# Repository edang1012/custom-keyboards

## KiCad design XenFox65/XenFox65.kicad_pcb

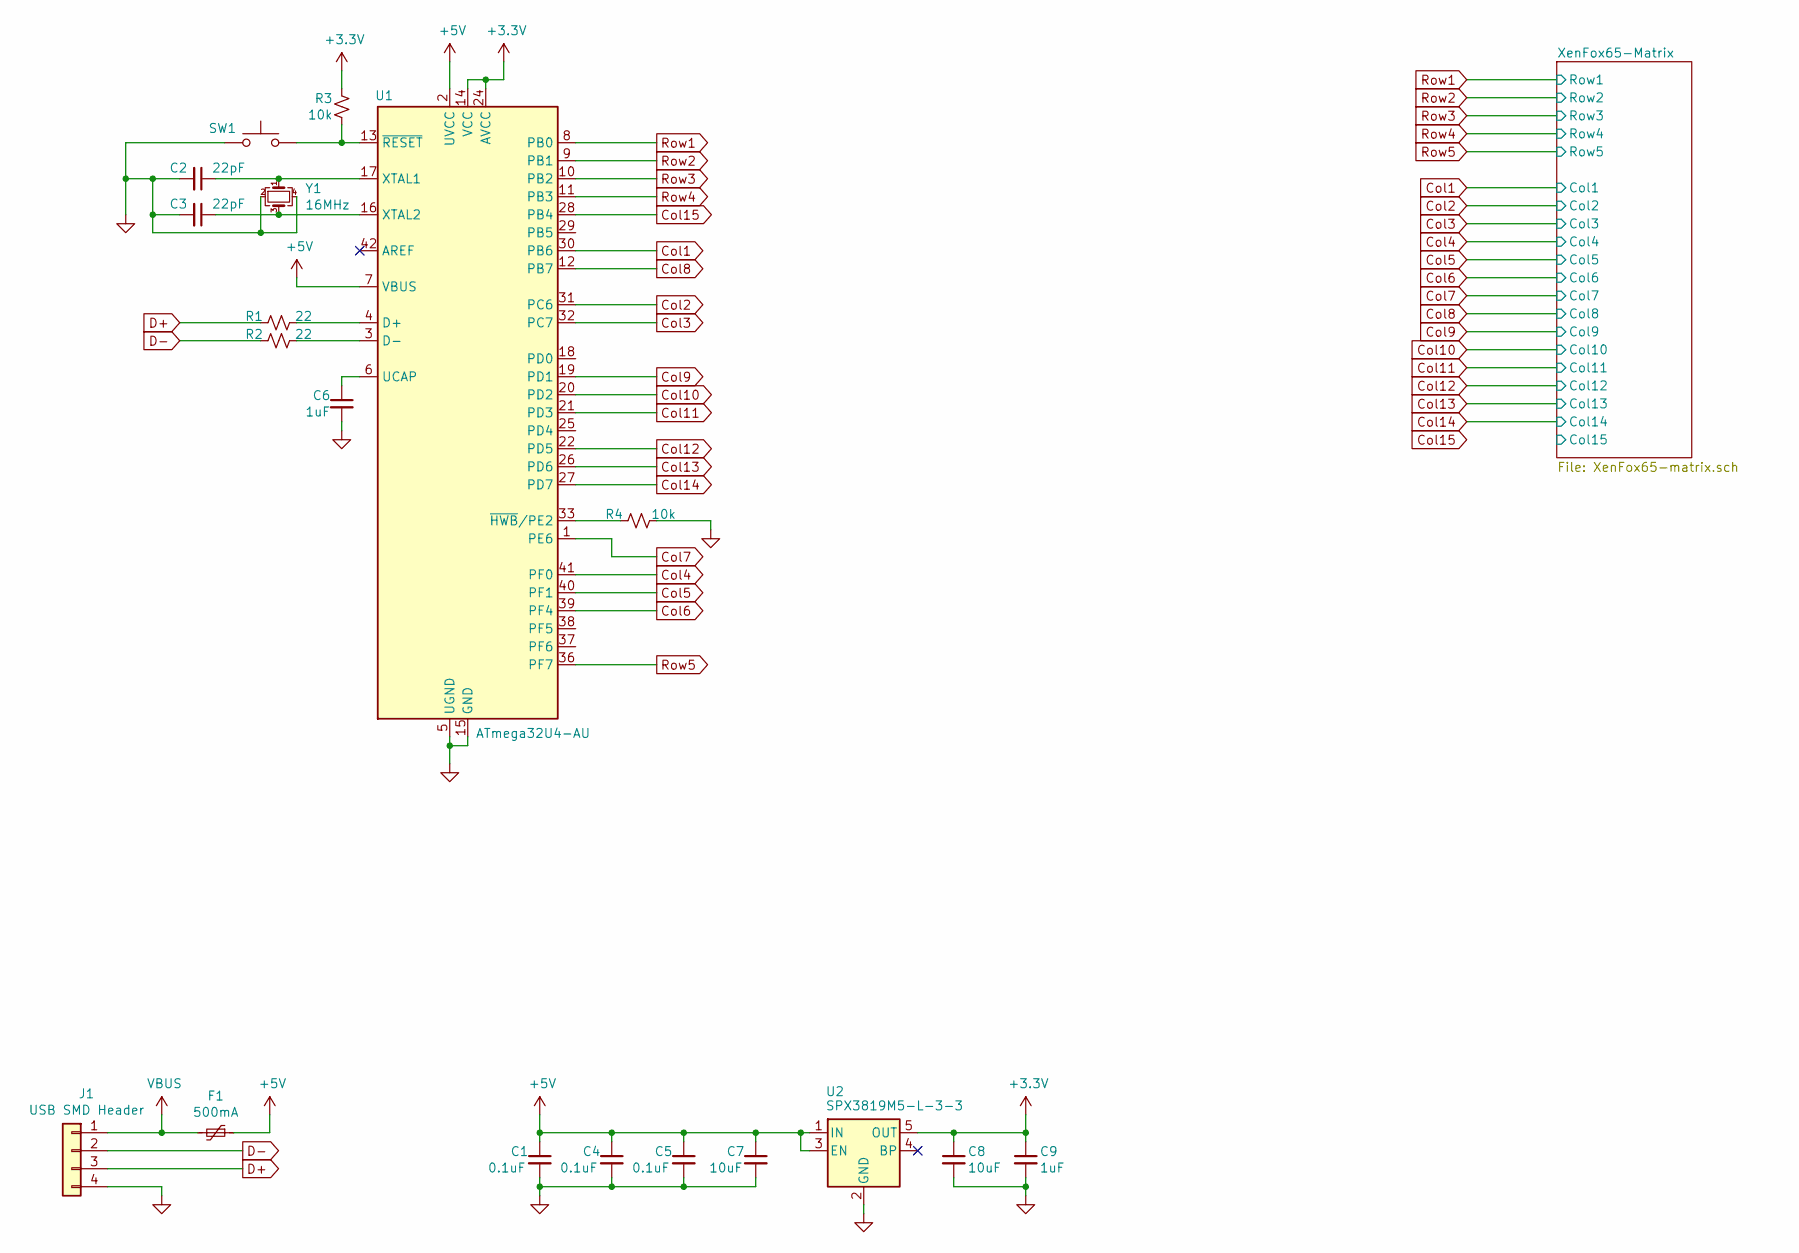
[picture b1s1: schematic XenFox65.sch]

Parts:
C1, C4, C5: 0.1uF; C_0805_2012Metric
C2, C3: 22pF; C_0805_2012Metric
C6, C9: 1uF; C_0805_2012Metric
C7, C8: 10uF; C_0805_2012Metric
F1: 500mA; Fuse_1206_3216Metric_Pad1.42x1.75mm_HandSolder
J1: USB SMD Header; S4B-ZR
R1, R2: 22; R_0805_2012Metric_Pad1.15x1.40mm_HandSolder
R3, R4: 10k; R_0805_2012Metric_Pad1.15x1.40mm_HandSolder
SW1: SW_Push; SKQG-1155865
U1: ATmega32U4-AU; TQFP-44_10x10mm_P0.8mm
U2: SPX3819M5-L-3-3; SOT-23-5
Y1: 16MHz; Crystal_SMD_3225-4Pin_3.2x2.5mm_HandSoldering

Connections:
+3V3: C8.1, C9.1, R3.1, U1.14 (VCC), U1.24 (AVCC), U1.34 (VCC), U1.44 (AVCC), U2.5 (OUT)
+5V: C1.1, C4.1, C5.1, C7.1, F1.1, U1.2 (UVCC), U1.7 (VBUS), U2.1 (IN), U2.3 (EN)
Col1: U1.30 (PB6); also elsewhere on the board
Col2: U1.31 (PC6); also elsewhere on the board
Col3: U1.32 (PC7); also elsewhere on the board
Col4: U1.41 (PF0); also elsewhere on the board
Col5: U1.40 (PF1); also elsewhere on the board
Col6: U1.39 (PF4); also elsewhere on the board
Col7: U1.1 (PE6); also elsewhere on the board
Col8: U1.12 (PB7); also elsewhere on the board
Col9: U1.19 (PD1); also elsewhere on the board
Col10: U1.20 (PD2); also elsewhere on the board
Col11: U1.21 (PD3); also elsewhere on the board
Col12: U1.22 (PD5); also elsewhere on the board
Col13: U1.26 (PD6); also elsewhere on the board
Col14: U1.27 (PD7); also elsewhere on the board
Col15: U1.28 (PB4); also elsewhere on the board
D+: J1.3, R1.2
D-: J1.2, R2.2
GND: C1.2, C2.2, C3.2, C4.2, C5.2, C6.2, C7.2, C8.2, C9.2, J1.4, R4.1, SW1.1, U1.5 (UGND), U1.15 (GND), U1.23 (GND), U1.35 (GND), U1.43 (GND), U2.2 (GND), Y1.2, Y1.4
unnamed: C2.1, U1.17 (XTAL1), Y1.1
unnamed: C3.1, U1.16 (XTAL2), Y1.3
unnamed: C6.1, U1.6 (UCAP)
unnamed: R1.1, U1.4 (D+)
unnamed: R2.1, U1.3 (D-)
unnamed: R3.2, SW1.2, U1.13 (~RESET)
unnamed: R4.2, U1.33 (~HWB~/PE2)
Row1: U1.8 (PB0); also elsewhere on the board
Row2: U1.9 (PB1); also elsewhere on the board
Row3: U1.10 (PB2); also elsewhere on the board
Row4: U1.11 (PB3); also elsewhere on the board
Row5: U1.36 (PF7); also elsewhere on the board
VBUS: F1.2, J1.1

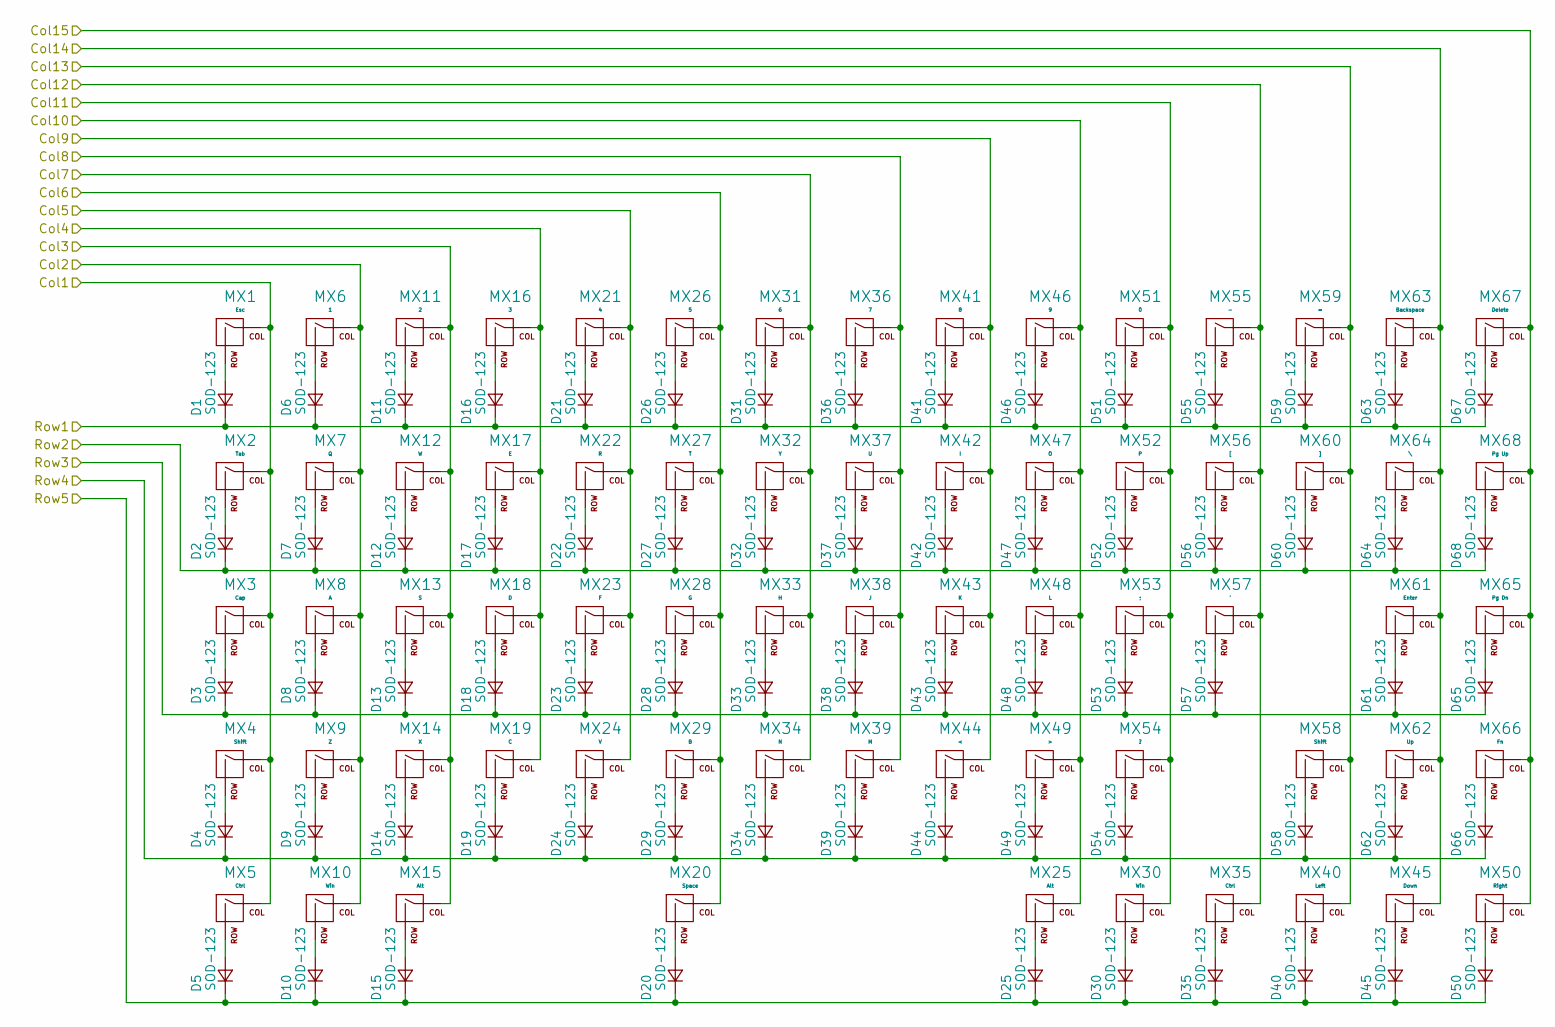
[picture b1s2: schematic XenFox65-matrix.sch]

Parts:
D1, D2, D3, D4, D5, D6, D7, D8, D9, D10, D11, D12, D13, D14, D15, D16, D17, D18, D19, D20, D21, D22, D23, D24, D25, D26, D27, D28, D29, D30, D31, D32, D33, D34, D35, D36, D37, D38, D39, D40, D41, D42, D43, D44, D45, D46, D47, D48, D49, D50, D51, D52, D53, D54, D55, D56, D57, D58, D59, D60, D61, D62, D63, D64, D65, D66, D67, D68: SOD-123; D_SOD-123
MX1: Esc; MXOnly-1U-NoLED
MX2: Tab; MXOnly-1.5U-NoLED
MX3: Cap; MXOnly-1.75U-NoLED
MX4: Shift; MXOnly-2.25U-NoLED
MX5: Ctrl; MXOnly-1.25U-NoLED
MX6: 1; MXOnly-1U-NoLED
MX7: Q; MXOnly-1U-NoLED
MX8: A; MXOnly-1U-NoLED
MX9: Z; MXOnly-1U-NoLED
MX10: Win; MXOnly-1.25U-NoLED
MX11: 2; MXOnly-1U-NoLED
MX12: W; MXOnly-1U-NoLED
MX13: S; MXOnly-1U-NoLED
MX14: X; MXOnly-1U-NoLED
MX15: Alt; MXOnly-1.25U-NoLED
MX16: 3; MXOnly-1U-NoLED
MX17: E; MXOnly-1U-NoLED
MX18: D; MXOnly-1U-NoLED
MX19: C; MXOnly-1U-NoLED
MX20: Space; MXOnly-6.25U-ReversedStabilizers-NoLED
MX21: 4; MXOnly-1U-NoLED
MX22: R; MXOnly-1U-NoLED
MX23: F; MXOnly-1U-NoLED
MX24: V; MXOnly-1U-NoLED
MX25: Alt; MXOnly-1U-NoLED
MX26: 5; MXOnly-1U-NoLED
MX27: T; MXOnly-1U-NoLED
MX28: G; MXOnly-1U-NoLED
MX29: B; MXOnly-1U-NoLED
MX30: Win; MXOnly-1U-NoLED
MX31: 6; MXOnly-1U-NoLED
MX32: Y; MXOnly-1U-NoLED
MX33: H; MXOnly-1U-NoLED
MX34: N; MXOnly-1U-NoLED
MX35: Ctrl; MXOnly-1U-NoLED
MX36: 7; MXOnly-1U-NoLED
MX37: U; MXOnly-1U-NoLED
MX38: J; MXOnly-1U-NoLED
MX39: M; MXOnly-1U-NoLED
MX40: Left; MXOnly-1U-NoLED
MX41: 8; MXOnly-1U-NoLED
MX42: I; MXOnly-1U-NoLED
MX43: K; MXOnly-1U-NoLED
MX44: <; MXOnly-1U-NoLED
MX45: Down; MXOnly-1U-NoLED
MX46: 9; MXOnly-1U-NoLED
MX47: O; MXOnly-1U-NoLED
MX48: L; MXOnly-1U-NoLED
MX49: >; MXOnly-1U-NoLED
MX50: Right; MXOnly-1U-NoLED
MX51: 0; MXOnly-1U-NoLED
MX52: P; MXOnly-1U-NoLED
MX53: ;; MXOnly-1U-NoLED
MX54: ?; MXOnly-1U-NoLED
MX55: -; MXOnly-1U-NoLED
MX56: [; MXOnly-1U-NoLED
MX57: '; MXOnly-1U-NoLED
MX58: Shift; MXOnly-1.75U-NoLED
MX59: =; MXOnly-1U-NoLED
MX60: ]; MXOnly-1U-NoLED
MX61: Enter; MXOnly-2.25U-NoLED
MX62: Up; MXOnly-1U-NoLED
MX63: Backspace; MXOnly-2U-NoLED
MX64: \\; MXOnly-1.5U-NoLED
MX65: Pg Dn; MXOnly-1U-NoLED
MX66: Fn; MXOnly-1U-NoLED
MX67: Delete; MXOnly-1U-NoLED
MX68: Pg Up; MXOnly-1U-NoLED

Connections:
Col1: MX1.1 (COL), MX2.1 (COL), MX3.1 (COL), MX4.1 (COL), MX5.1 (COL); also elsewhere on the board
Col2: MX6.1 (COL), MX7.1 (COL), MX8.1 (COL), MX9.1 (COL), MX10.1 (COL); also elsewhere on the board
Col3: MX11.1 (COL), MX12.1 (COL), MX13.1 (COL), MX14.1 (COL), MX15.1 (COL); also elsewhere on the board
Col4: MX16.1 (COL), MX17.1 (COL), MX18.1 (COL), MX19.1 (COL); also elsewhere on the board
Col5: MX21.1 (COL), MX22.1 (COL), MX23.1 (COL), MX24.1 (COL); also elsewhere on the board
Col6: MX20.1 (COL), MX26.1 (COL), MX27.1 (COL), MX28.1 (COL), MX29.1 (COL); also elsewhere on the board
Col7: MX31.1 (COL), MX32.1 (COL), MX33.1 (COL), MX34.1 (COL); also elsewhere on the board
Col8: MX36.1 (COL), MX37.1 (COL), MX38.1 (COL), MX39.1 (COL); also elsewhere on the board
Col9: MX41.1 (COL), MX42.1 (COL), MX43.1 (COL), MX44.1 (COL); also elsewhere on the board
Col10: MX25.1 (COL), MX46.1 (COL), MX47.1 (COL), MX48.1 (COL), MX49.1 (COL); also elsewhere on the board
Col11: MX30.1 (COL), MX51.1 (COL), MX52.1 (COL), MX53.1 (COL), MX54.1 (COL); also elsewhere on the board
Col12: MX35.1 (COL), MX55.1 (COL), MX56.1 (COL), MX57.1 (COL); also elsewhere on the board
Col13: MX40.1 (COL), MX58.1 (COL), MX59.1 (COL), MX60.1 (COL); also elsewhere on the board
Col14: MX45.1 (COL), MX61.1 (COL), MX62.1 (COL), MX63.1 (COL), MX64.1 (COL); also elsewhere on the board
Col15: MX50.1 (COL), MX65.1 (COL), MX66.1 (COL), MX67.1 (COL), MX68.1 (COL); also elsewhere on the board
unnamed: D1.2 (A), MX1.2 (ROW)
unnamed: D2.2 (A), MX2.2 (ROW)
unnamed: D3.2 (A), MX3.2 (ROW)
unnamed: D4.2 (A), MX4.2 (ROW)
unnamed: D5.2 (A), MX5.2 (ROW)
unnamed: D6.2 (A), MX6.2 (ROW)
unnamed: D7.2 (A), MX7.2 (ROW)
unnamed: D8.2 (A), MX8.2 (ROW)
unnamed: D9.2 (A), MX9.2 (ROW)
unnamed: D10.2 (A), MX10.2 (ROW)
unnamed: D11.2 (A), MX11.2 (ROW)
unnamed: D12.2 (A), MX12.2 (ROW)
unnamed: D13.2 (A), MX13.2 (ROW)
unnamed: D14.2 (A), MX14.2 (ROW)
unnamed: D15.2 (A), MX15.2 (ROW)
unnamed: D16.2 (A), MX16.2 (ROW)
unnamed: D17.2 (A), MX17.2 (ROW)
unnamed: D18.2 (A), MX18.2 (ROW)
unnamed: D19.2 (A), MX19.2 (ROW)
unnamed: D20.2 (A), MX20.2 (ROW)
unnamed: D21.2 (A), MX21.2 (ROW)
unnamed: D22.2 (A), MX22.2 (ROW)
unnamed: D23.2 (A), MX23.2 (ROW)
unnamed: D24.2 (A), MX24.2 (ROW)
unnamed: D25.2 (A), MX25.2 (ROW)
unnamed: D26.2 (A), MX26.2 (ROW)
unnamed: D27.2 (A), MX27.2 (ROW)
unnamed: D28.2 (A), MX28.2 (ROW)
unnamed: D29.2 (A), MX29.2 (ROW)
unnamed: D30.2 (A), MX30.2 (ROW)
unnamed: D31.2 (A), MX31.2 (ROW)
unnamed: D32.2 (A), MX32.2 (ROW)
unnamed: D33.2 (A), MX33.2 (ROW)
unnamed: D34.2 (A), MX34.2 (ROW)
unnamed: D35.2 (A), MX35.2 (ROW)
unnamed: D36.2 (A), MX36.2 (ROW)
unnamed: D37.2 (A), MX37.2 (ROW)
unnamed: D38.2 (A), MX38.2 (ROW)
unnamed: D39.2 (A), MX39.2 (ROW)
unnamed: D40.2 (A), MX40.2 (ROW)
unnamed: D41.2 (A), MX41.2 (ROW)
unnamed: D42.2 (A), MX42.2 (ROW)
unnamed: D43.2 (A), MX43.2 (ROW)
unnamed: D44.2 (A), MX44.2 (ROW)
unnamed: D45.2 (A), MX45.2 (ROW)
unnamed: D46.2 (A), MX46.2 (ROW)
unnamed: D47.2 (A), MX47.2 (ROW)
unnamed: D48.2 (A), MX48.2 (ROW)
unnamed: D49.2 (A), MX49.2 (ROW)
unnamed: D50.2 (A), MX50.2 (ROW)
unnamed: D51.2 (A), MX51.2 (ROW)
unnamed: D52.2 (A), MX52.2 (ROW)
unnamed: D53.2 (A), MX53.2 (ROW)
unnamed: D54.2 (A), MX54.2 (ROW)
unnamed: D55.2 (A), MX55.2 (ROW)
unnamed: D56.2 (A), MX56.2 (ROW)
unnamed: D57.2 (A), MX57.2 (ROW)
unnamed: D58.2 (A), MX58.2 (ROW)
unnamed: D59.2 (A), MX59.2 (ROW)
unnamed: D60.2 (A), MX60.2 (ROW)
unnamed: D61.2 (A), MX61.2 (ROW)
unnamed: D62.2 (A), MX62.2 (ROW)
unnamed: D63.2 (A), MX63.2 (ROW)
unnamed: D64.2 (A), MX64.2 (ROW)
unnamed: D65.2 (A), MX65.2 (ROW)
unnamed: D66.2 (A), MX66.2 (ROW)
unnamed: D67.2 (A), MX67.2 (ROW)
unnamed: D68.2 (A), MX68.2 (ROW)
Row1: D1.1 (K), D6.1 (K), D11.1 (K), D16.1 (K), D21.1 (K), D26.1 (K), D31.1 (K), D36.1 (K), D41.1 (K), D46.1 (K), D51.1 (K), D55.1 (K), D59.1 (K), D63.1 (K), D67.1 (K); also elsewhere on the board
Row2: D2.1 (K), D7.1 (K), D12.1 (K), D17.1 (K), D22.1 (K), D27.1 (K), D32.1 (K), D37.1 (K), D42.1 (K), D47.1 (K), D52.1 (K), D56.1 (K), D60.1 (K), D64.1 (K), D68.1 (K); also elsewhere on the board
Row3: D3.1 (K), D8.1 (K), D13.1 (K), D18.1 (K), D23.1 (K), D28.1 (K), D33.1 (K), D38.1 (K), D43.1 (K), D48.1 (K), D53.1 (K), D57.1 (K), D61.1 (K), D65.1 (K); also elsewhere on the board
Row4: D4.1 (K), D9.1 (K), D14.1 (K), D19.1 (K), D24.1 (K), D29.1 (K), D34.1 (K), D39.1 (K), D44.1 (K), D49.1 (K), D54.1 (K), D58.1 (K), D62.1 (K), D66.1 (K); also elsewhere on the board
Row5: D5.1 (K), D10.1 (K), D15.1 (K), D20.1 (K), D25.1 (K), D30.1 (K), D35.1 (K), D40.1 (K), D45.1 (K), D50.1 (K); also elsewhere on the board

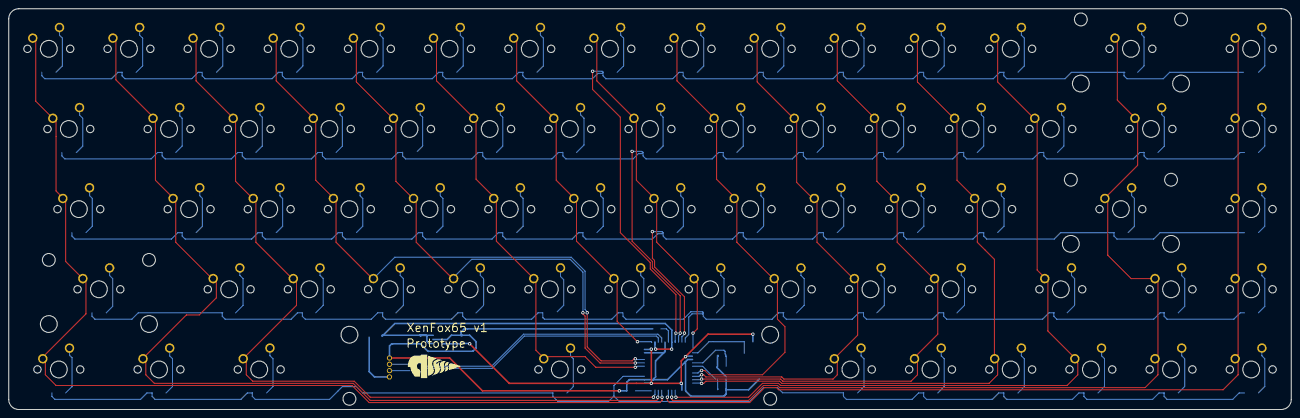
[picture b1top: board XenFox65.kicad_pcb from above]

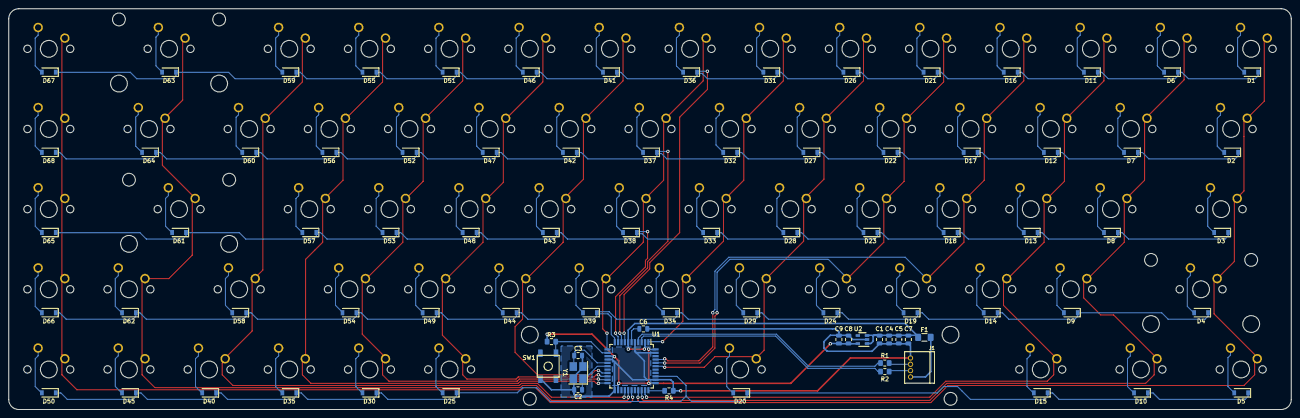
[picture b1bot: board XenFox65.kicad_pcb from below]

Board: 2 copper layers, 304.8 x 95.3 mm, 155 parts (87 on the bottom side), 101 nets.

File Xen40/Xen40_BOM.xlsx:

Ref. Des. | value
C1 | 0.1uF | 805 | DONE
C2 | 22pF | 805 | DONE
C3 | 22pF | 805 | DONE
C4 | 0.1uF | 805 | DONE
C5 | 0.1uF | 805 | DONE
C6 | 1uF | 805 | DONE
C7 | 10uF | 805 | DONE
C8 | 10uF | 805 | DONE
C9 | 1uF | 805 | DONE
C10 | 10uF | 805 | DONE
D1 | MBR120 | SOD-123 | DONE
D2 | O-LED | 805 | DONE
D3 | diode | SOD-123 | DONE
D4 | diode | SOD-123 | DONE
D5 | diode | SOD-123 | DONE
D6 | diode | SOD-123 | DONE
D7 | diode | SOD-123 | DONE
D8 | diode | SOD-123 | DONE
D9 | diode | SOD-123 | DONE
D10 | diode | SOD-123 | DONE
D11 | diode | SOD-123 | DONE
D12 | diode | SOD-123 | DONE
D13 | diode | SOD-123 | DONE
D14 | diode | SOD-123 | DONE
D15 | diode | SOD-123 | DONE
D16 | diode | SOD-123 | DONE
D17 | diode | SOD-123 | DONE
D18 | diode | SOD-123 | DONE
D19 | diode | SOD-123 | DONE
D20 | diode | SOD-123 | DONE
D21 | diode | SOD-123 | DONE
D22 | diode | SOD-123 | DONE
D23 | diode | SOD-123 | DONE
D24 | diode | SOD-123 | DONE
D25 | diode | SOD-123 | DONE
D26 | diode | SOD-123 | DONE
D27 | diode | SOD-123 | DONE
D28 | diode | SOD-123 | DONE
D29 | diode | SOD-123 | DONE
D30 | diode | SOD-123 | DONE
D31 | diode | SOD-123 | DONE
D32 | diode | SOD-123 | DONE
D33 | diode | SOD-123 | DONE
D34 | diode | SOD-123 | DONE
D35 | diode | SOD-123 | DONE
D36 | diode | SOD-123 | DONE
D37 | diode | SOD-123 | DONE
D38 | diode | SOD-123 | DONE
D39 | diode | SOD-123 | DONE
D40 | diode | SOD-123 | DONE
D41 | diode | SOD-123 | DONE
D42 | diode | SOD-123 | DONE
D43 | diode | SOD-123 | DONE
D44 | diode | SOD-123 | DONE
D45 | diode | SOD-123 | DONE
D46 | diode | SOD-123 | DONE
D47 | G-LED | 805 | DONE
F1 | 500mA | 1206 | DONE
J1 | USB Header |  | DONE
J2 | BLE Header
J3 | OLED |  | DONE
J4 | BATT Header |  | DONE
MX1 | MX |  | DONE
MX2 | MX |  | DONE
MX3 | MX |  | DONE
MX4 | MX |  | DONE
MX5 | MX |  | DONE
MX6 | MX |  | DONE
MX7 | MX |  | DONE
MX8 | MX |  | DONE
MX9 | MX |  | DONE
MX10 | MX |  | DONE
MX11 | MX |  | DONE
MX12 | MX |  | DONE
MX13 | MX |  | DONE
MX14 | MX |  | DONE
MX15 | MX |  | DONE
MX16 | MX |  | DONE
MX17 | MX |  | DONE
MX18 | MX |  | DONE
MX19 | MX |  | DONE
MX20 | MX |  | DONE
MX21 | MX |  | DONE
MX22 | MX |  | DONE
MX23 | MX |  | DONE
MX24 | MX |  | DONE
MX25 | MX |  | DONE
MX26 | MX |  | DONE
MX27 | MX |  | DONE
MX28 | MX |  | DONE
MX29 | MX |  | DONE
MX30 | MX |  | DONE
MX31 | MX |  | DONE
MX32 | MX |  | DONE
MX33 | MX |  | DONE
MX34 | MX |  | DONE
MX35 | MX |  | DONE
MX36 | MX |  | DONE
MX37 | MX |  | DONE
MX38 | MX |  | DONE
MX39 | MX |  | DONE
MX40 | MX |  | DONE
MX41 | MX |  | DONE
MX42 | MX |  | DONE
MX43 | MX |  | DONE
MX44 | MX |  | DONE
R1 | 22 |  | DONE
R2 | 22 |  | DONE
R3 | 10k |  | DONE
R4 | 10k |  | DONE
R5 | 10k |  | DONE
R6 | 470 |  | DONE
R8 | 470 |  | DONE
SW1 |  |  | DONE
U1 | ATmega32u4 |  | DONE
U2 | SPX3819 | SOT-23-5 | DONE
U3 | MCP73831 | SOT-23-6 | DONE
Y1 | 16MHz | 3325-4pin | DONE

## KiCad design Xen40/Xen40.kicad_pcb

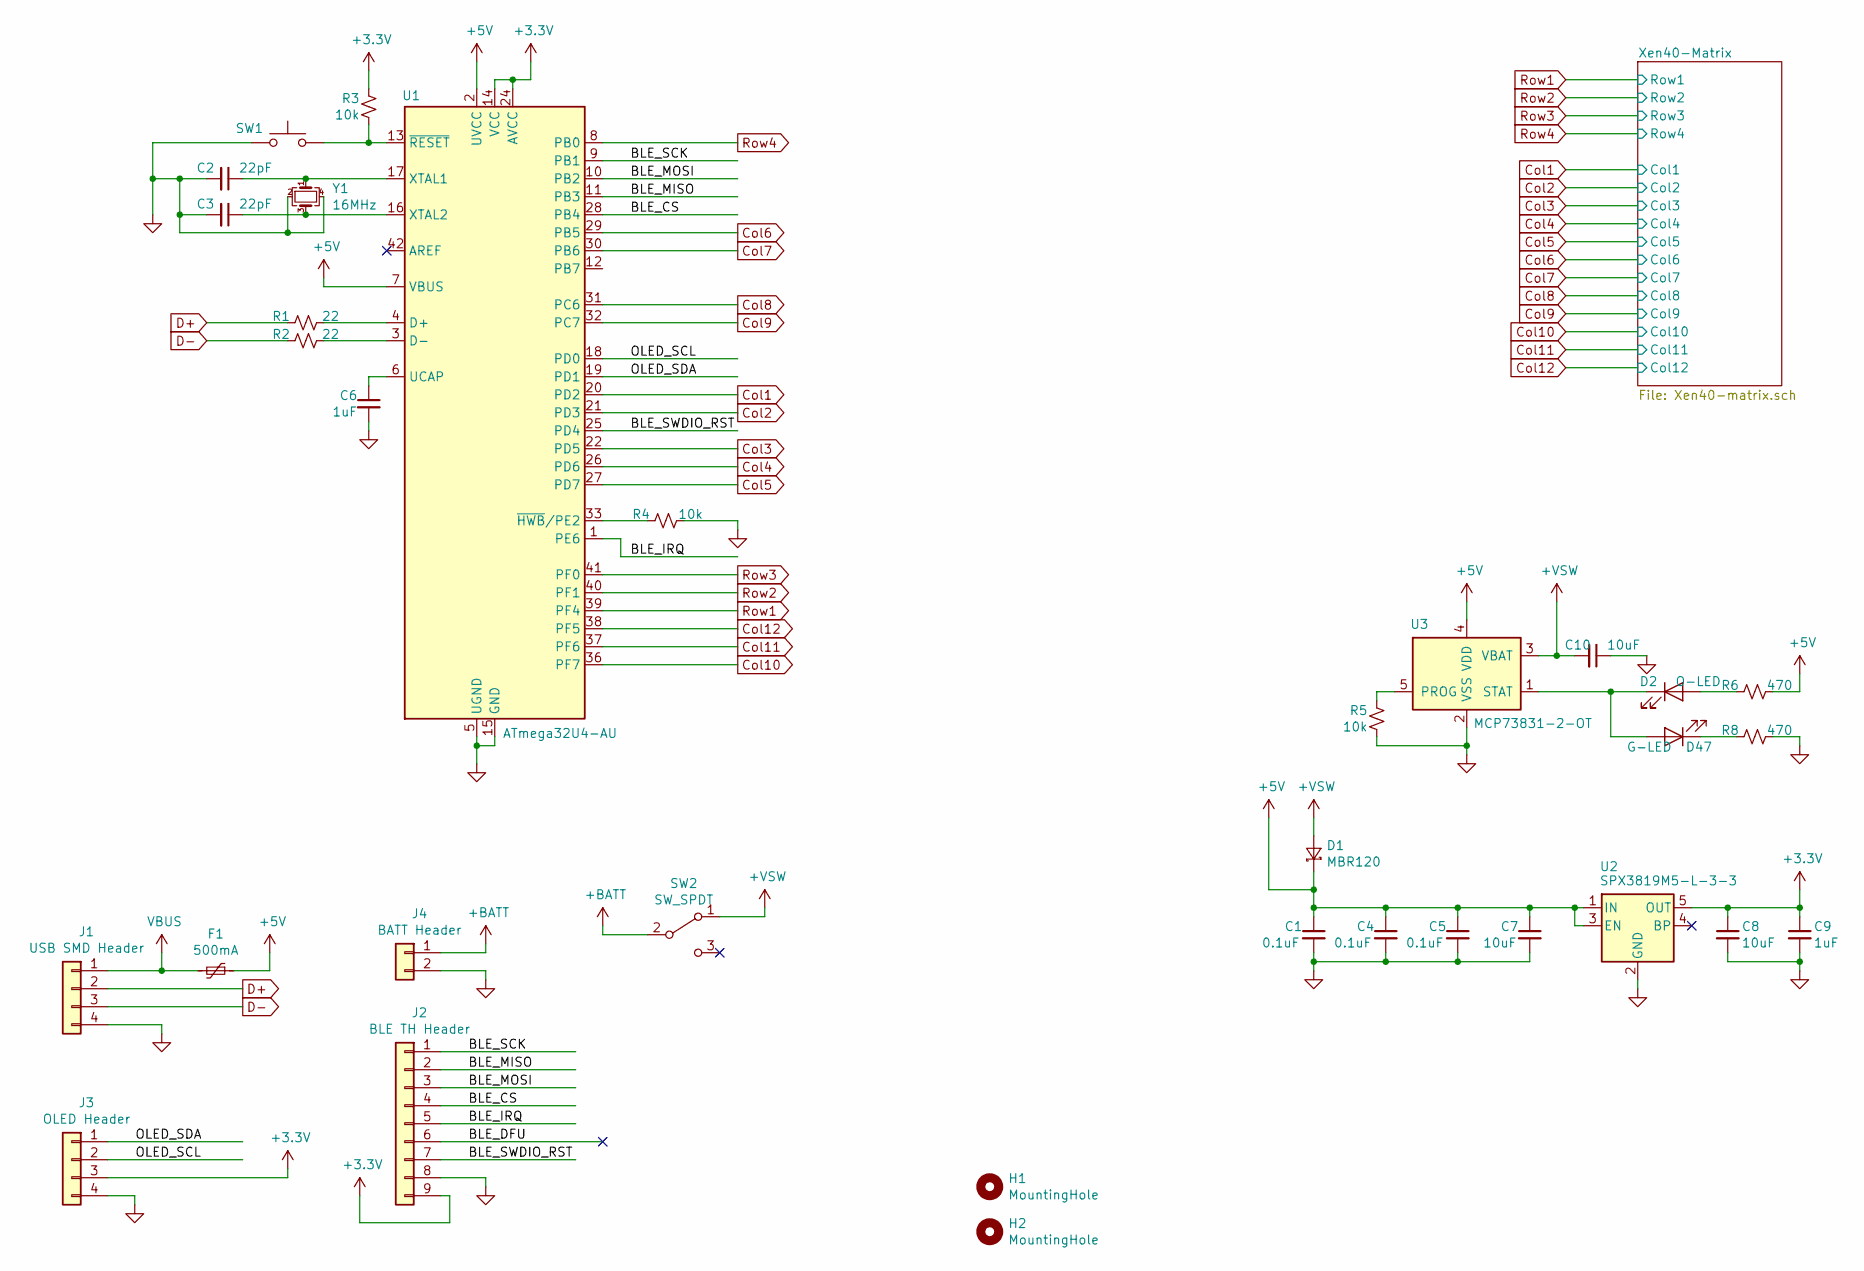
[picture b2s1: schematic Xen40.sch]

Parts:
C1, C4, C5: 0.1uF; C_0805_2012Metric
C2, C3: 22pF; C_0805_2012Metric
C6, C9: 1uF; C_0805_2012Metric
C7, C8, C10: 10uF; C_0805_2012Metric
D1: MBR120; D_SOD-123
D2: O-LED; LED_0805_2012Metric_Pad1.15x1.40mm_HandSolder
D47: G-LED; LED_0805_2012Metric_Pad1.15x1.40mm_HandSolder
F1: 500mA; Fuse_1206_3216Metric_Pad1.42x1.75mm_HandSolder
H1, H2: MountingHole; MOUNTINGHOLE_2.5_PLATED
J1: USB SMD Header; S4B-ZR
J2: BLE TH Header; 1X09_ROUND_70
J3: OLED Header; OLED_4Pin
J4: BATT Header; S2B-PH-K-S
R1, R2: 22; R_0805_2012Metric_Pad1.15x1.40mm_HandSolder
R3, R4, R5: 10k; R_0805_2012Metric_Pad1.15x1.40mm_HandSolder
R6, R8: 470; R_0805_2012Metric_Pad1.15x1.40mm_HandSolder
SW1: SW_Push; SKQG-1155865
SW2: SW_SPDT; Batt_SW
U1: ATmega32U4-AU; TQFP-44_10x10mm_P0.8mm
U2: SPX3819M5-L-3-3; SOT-23-5
U3: MCP73831-2-OT; SOT-23-5
Y1: 16MHz; Crystal_SMD_3225-4Pin_3.2x2.5mm_HandSoldering

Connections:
+3V3: C8.1, C9.1, J2.9, J3.3, R3.1, U1.14 (VCC), U1.24 (AVCC), U1.34 (VCC), U1.44 (AVCC), U2.5 (OUT)
+5V: C1.1, C4.1, C5.1, C7.1, D1.1 (K), F1.1, R6.1, U1.2 (UVCC), U1.7 (VBUS), U2.1 (IN), U2.3 (EN), U3.4 (VDD)
+BATT: J4.1, SW2.2 (B)
+VSW: C10.2, D1.2 (A), SW2.1 (A), U3.3 (VBAT)
/BLE_CS: J2.4, U1.28 (PB4)
/BLE_DFU: J2.6
/BLE_IRQ: J2.5, U1.1 (PE6)
/BLE_MISO: J2.2, U1.11 (PB3)
/BLE_MOSI: J2.3, U1.10 (PB2)
/BLE_SCK: J2.1, U1.9 (PB1)
/BLE_SWDIO_RST: J2.7, U1.25 (PD4)
/OLED_SCL: J3.2, U1.18 (PD0)
/OLED_SDA: J3.1, U1.19 (PD1)
Col1: U1.20 (PD2); also elsewhere on the board
Col2: U1.21 (PD3); also elsewhere on the board
Col3: U1.22 (PD5); also elsewhere on the board
Col4: U1.26 (PD6); also elsewhere on the board
Col5: U1.27 (PD7); also elsewhere on the board
Col6: U1.29 (PB5); also elsewhere on the board
Col7: U1.30 (PB6); also elsewhere on the board
Col8: U1.31 (PC6); also elsewhere on the board
Col9: U1.32 (PC7); also elsewhere on the board
Col10: U1.36 (PF7); also elsewhere on the board
Col11: U1.37 (PF6); also elsewhere on the board
Col12: U1.38 (PF5); also elsewhere on the board
D+: J1.2, R1.2
D-: J1.3, R2.2
GND: C1.2, C2.2, C3.2, C4.2, C5.2, C6.2, C7.2, C8.2, C9.2, C10.1, J1.4, J2.8, J3.4, J4.2, R4.1, R5.2, R8.1, SW1.1, U1.5 (UGND), U1.15 (GND), U1.23 (GND), U1.35 (GND), U1.43 (GND), U2.2 (GND), U3.2 (VSS), Y1.2, Y1.4
unnamed: C2.1, U1.17 (XTAL1), Y1.1
unnamed: C3.1, U1.16 (XTAL2), Y1.3
unnamed: C6.1, U1.6 (UCAP)
unnamed: D2.1 (K), D47.2 (A), U3.1 (STAT)
unnamed: D2.2 (A), R6.2
unnamed: D47.1 (K), R8.2
unnamed: R1.1, U1.4 (D+)
unnamed: R2.1, U1.3 (D-)
unnamed: R3.2, SW1.2, U1.13 (~RESET)
unnamed: R4.2, U1.33 (~HWB~/PE2)
unnamed: R5.1, U3.5 (PROG)
Row1: U1.39 (PF4); also elsewhere on the board
Row2: U1.40 (PF1); also elsewhere on the board
Row3: U1.41 (PF0); also elsewhere on the board
Row4: U1.8 (PB0); also elsewhere on the board
VBUS: F1.2, J1.1

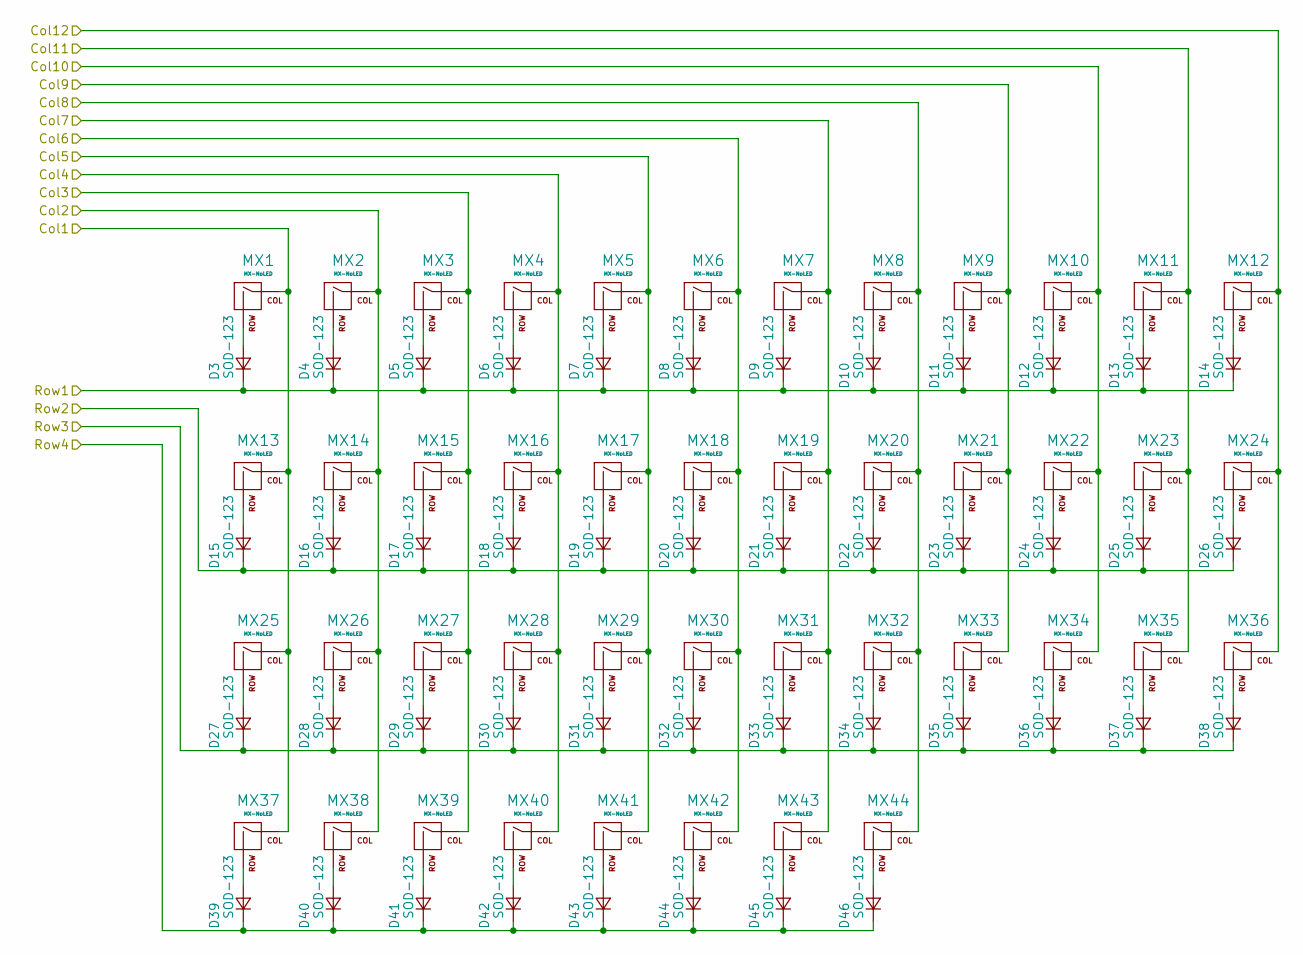
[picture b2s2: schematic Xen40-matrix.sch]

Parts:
D3, D4, D5, D6, D7, D8, D9, D10, D11, D12, D13, D14, D15, D16, D17, D18, D19, D20, D21, D22, D23, D24, D25, D26, D27, D28, D29, D30, D31, D32, D33, D34, D35, D36, D37, D38, D39, D40, D41, D42, D43, D44, D45, D46: SOD-123; D_SOD-123
MX1, MX2, MX3, MX4, MX5, MX6, MX7, MX8, MX9, MX10, MX11, MX12, MX13, MX14, MX15, MX16, MX17, MX18, MX19, MX20, MX21, MX22, MX23, MX24, MX25, MX26, MX27, MX28, MX29, MX30, MX31, MX32, MX33, MX34, MX35, MX36, MX42, MX43: MX-NoLED; MXOnly-1U-NoLED
MX37, MX38, MX40, MX44: MX-NoLED; MXOnly-1.25U-NoLED
MX39: MX-NoLED; MXOnly-2.25U-ReversedStabilizers-NoLED
MX41: MX-NoLED; MXOnly-2.75U-ReversedStabilizers-NoLED

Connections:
Col1: MX1.1 (COL), MX13.1 (COL), MX25.1 (COL), MX37.1 (COL); also elsewhere on the board
Col2: MX2.1 (COL), MX14.1 (COL), MX26.1 (COL), MX38.1 (COL); also elsewhere on the board
Col3: MX3.1 (COL), MX15.1 (COL), MX27.1 (COL), MX39.1 (COL); also elsewhere on the board
Col4: MX4.1 (COL), MX16.1 (COL), MX28.1 (COL), MX40.1 (COL); also elsewhere on the board
Col5: MX5.1 (COL), MX17.1 (COL), MX29.1 (COL), MX41.1 (COL); also elsewhere on the board
Col6: MX6.1 (COL), MX18.1 (COL), MX30.1 (COL), MX42.1 (COL); also elsewhere on the board
Col7: MX7.1 (COL), MX19.1 (COL), MX31.1 (COL), MX43.1 (COL); also elsewhere on the board
Col8: MX8.1 (COL), MX20.1 (COL), MX32.1 (COL), MX44.1 (COL); also elsewhere on the board
Col9: MX9.1 (COL), MX21.1 (COL), MX33.1 (COL); also elsewhere on the board
Col10: MX10.1 (COL), MX22.1 (COL), MX34.1 (COL); also elsewhere on the board
Col11: MX11.1 (COL), MX23.1 (COL), MX35.1 (COL); also elsewhere on the board
Col12: MX12.1 (COL), MX24.1 (COL), MX36.1 (COL); also elsewhere on the board
unnamed: D3.2 (A), MX1.2 (ROW)
unnamed: D4.2 (A), MX2.2 (ROW)
unnamed: D5.2 (A), MX3.2 (ROW)
unnamed: D6.2 (A), MX4.2 (ROW)
unnamed: D7.2 (A), MX5.2 (ROW)
unnamed: D8.2 (A), MX6.2 (ROW)
unnamed: D9.2 (A), MX7.2 (ROW)
unnamed: D10.2 (A), MX8.2 (ROW)
unnamed: D11.2 (A), MX9.2 (ROW)
unnamed: D12.2 (A), MX10.2 (ROW)
unnamed: D13.2 (A), MX11.2 (ROW)
unnamed: D14.2 (A), MX12.2 (ROW)
unnamed: D15.2 (A), MX13.2 (ROW)
unnamed: D16.2 (A), MX14.2 (ROW)
unnamed: D17.2 (A), MX15.2 (ROW)
unnamed: D18.2 (A), MX16.2 (ROW)
unnamed: D19.2 (A), MX17.2 (ROW)
unnamed: D20.2 (A), MX18.2 (ROW)
unnamed: D21.2 (A), MX19.2 (ROW)
unnamed: D22.2 (A), MX20.2 (ROW)
unnamed: D23.2 (A), MX21.2 (ROW)
unnamed: D24.2 (A), MX22.2 (ROW)
unnamed: D25.2 (A), MX23.2 (ROW)
unnamed: D26.2 (A), MX24.2 (ROW)
unnamed: D27.2 (A), MX25.2 (ROW)
unnamed: D28.2 (A), MX26.2 (ROW)
unnamed: D29.2 (A), MX27.2 (ROW)
unnamed: D30.2 (A), MX28.2 (ROW)
unnamed: D31.2 (A), MX29.2 (ROW)
unnamed: D32.2 (A), MX30.2 (ROW)
unnamed: D33.2 (A), MX31.2 (ROW)
unnamed: D34.2 (A), MX32.2 (ROW)
unnamed: D35.2 (A), MX33.2 (ROW)
unnamed: D36.2 (A), MX34.2 (ROW)
unnamed: D37.2 (A), MX35.2 (ROW)
unnamed: D38.2 (A), MX36.2 (ROW)
unnamed: D39.2 (A), MX37.2 (ROW)
unnamed: D40.2 (A), MX38.2 (ROW)
unnamed: D41.2 (A), MX39.2 (ROW)
unnamed: D42.2 (A), MX40.2 (ROW)
unnamed: D43.2 (A), MX41.2 (ROW)
unnamed: D44.2 (A), MX42.2 (ROW)
unnamed: D45.2 (A), MX43.2 (ROW)
unnamed: D46.2 (A), MX44.2 (ROW)
Row1: D3.1 (K), D4.1 (K), D5.1 (K), D6.1 (K), D7.1 (K), D8.1 (K), D9.1 (K), D10.1 (K), D11.1 (K), D12.1 (K), D13.1 (K), D14.1 (K); also elsewhere on the board
Row2: D15.1 (K), D16.1 (K), D17.1 (K), D18.1 (K), D19.1 (K), D20.1 (K), D21.1 (K), D22.1 (K), D23.1 (K), D24.1 (K), D25.1 (K), D26.1 (K); also elsewhere on the board
Row3: D27.1 (K), D28.1 (K), D29.1 (K), D30.1 (K), D31.1 (K), D32.1 (K), D33.1 (K), D34.1 (K), D35.1 (K), D36.1 (K), D37.1 (K), D38.1 (K); also elsewhere on the board
Row4: D39.1 (K), D40.1 (K), D41.1 (K), D42.1 (K), D43.1 (K), D44.1 (K), D45.1 (K), D46.1 (K); also elsewhere on the board

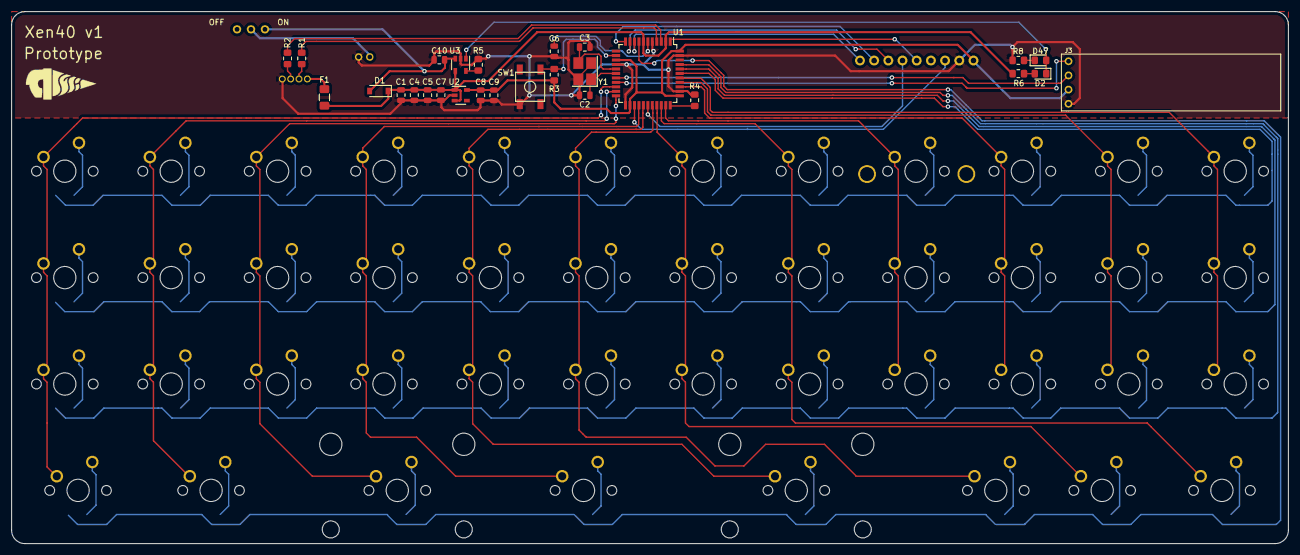
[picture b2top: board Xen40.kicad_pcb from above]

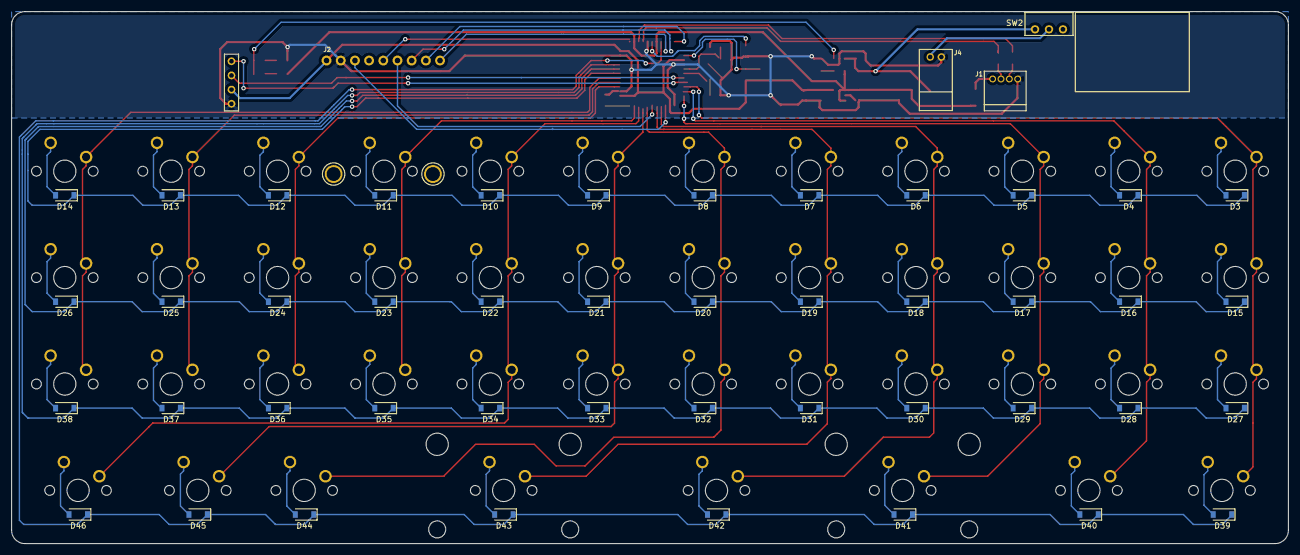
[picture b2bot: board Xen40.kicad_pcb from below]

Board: 2 copper layers, 228.6 x 95.3 mm, 121 parts (50 on the bottom side), 87 nets.

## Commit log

2020-03-16 Create keyboard-layout.png
    Temporary. Keysizes are probably final.
2020-03-16 Rename .gitattributes to Xen40/.gitattributes
2020-03-16 Rename README.md to Xen40/README.md
2020-03-16 Initialize Project
2020-03-16 Add submodules
2020-03-16 Add footprint libraries
2020-03-16 Progress on schematic
2020-04-10 new files
2020-05-14 Finished Initial Routing for V1
2020-06-08 Changed Location of Switch, Added Silkscreen
2020-12-30 update
    sadsad
2020-12-31 XenFox65
